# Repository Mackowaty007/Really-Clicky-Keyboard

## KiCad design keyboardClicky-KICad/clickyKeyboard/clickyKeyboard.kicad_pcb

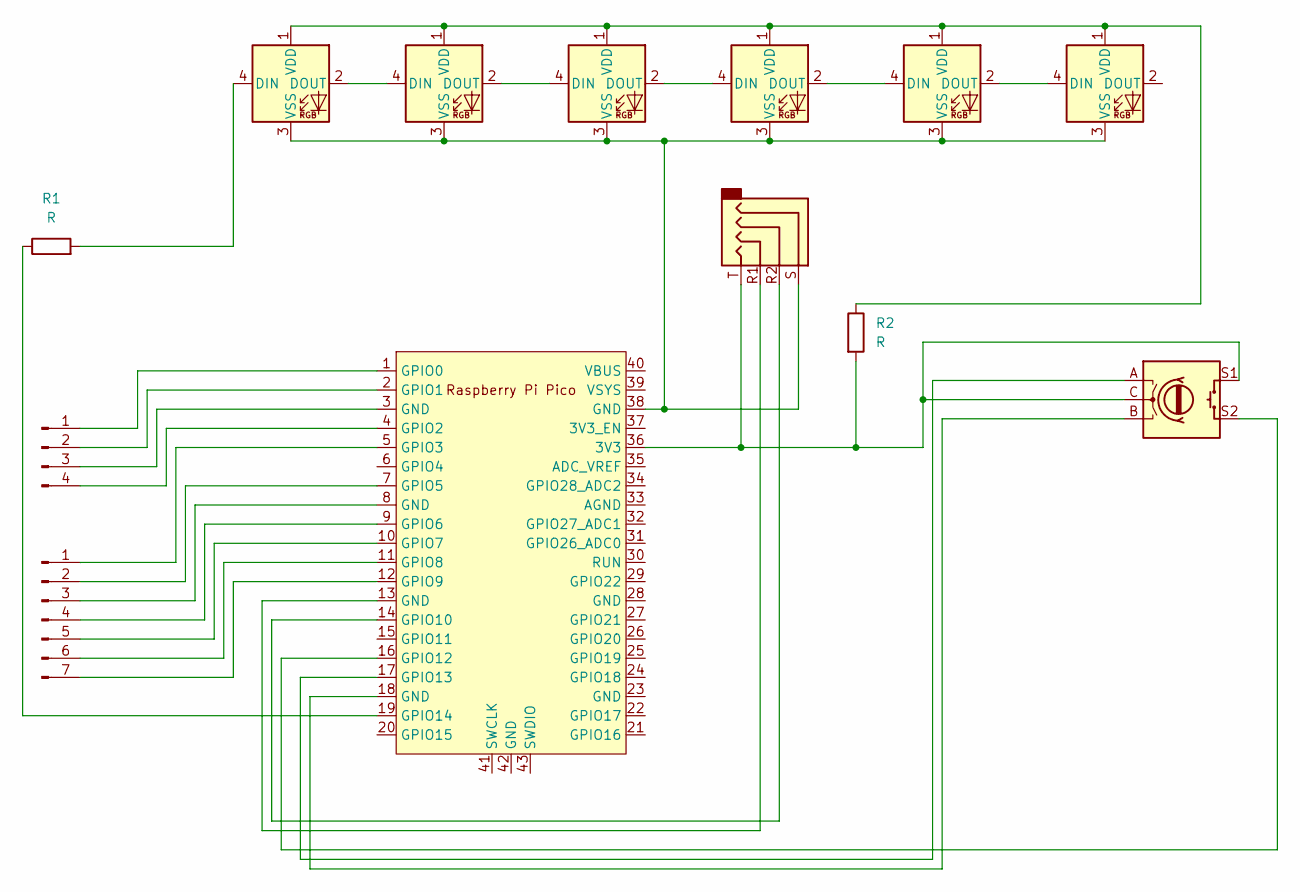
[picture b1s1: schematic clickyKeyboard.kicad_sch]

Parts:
D1, D2, D3, D4, D5, D6: WS2812B; LED_WS2812B_PLCC4_5.0x5.0mm_P3.2mm
J1: Conn_01x04_Pin; PinHeader_1x04_P2.54mm_Vertical
J2: Conn_01x07_Pin; PinHeader_1x07_P2.54mm_Vertical
J4: AudioJack4; Jack_3.5mm_KoreanHropartsElec_PJ-320D-4A_Horizontal
R1, R2: R; R_Axial_DIN0204_L3.6mm_D1.6mm_P7.62mm_Horizontal
SW1: RotaryEncoder_Switch; RotaryEncoder_Alps_EC11E-Switch_Vertical_H20mm
U1: Pico; RPi_Pico_SMD_TH

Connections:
unnamed: D1.4 (DIN), R1.2
unnamed: D1.2 (DOUT), D2.4 (DIN)
unnamed: D1.1 (VDD), D2.1 (VDD), D3.1 (VDD), D4.1 (VDD), D5.1 (VDD), D6.1 (VDD), R2.1
unnamed: D1.3 (VSS), D2.3 (VSS), D3.3 (VSS), D4.3 (VSS), D5.3 (VSS), D6.3 (VSS), J4.S, U1.38 (GND)
unnamed: D2.2 (DOUT), D3.4 (DIN)
unnamed: D3.2 (DOUT), D4.4 (DIN)
unnamed: D4.2 (DOUT), D5.4 (DIN)
unnamed: D5.2 (DOUT), D6.4 (DIN)
unnamed: J1.1, U1.1 (GPIO0)
unnamed: J1.2, U1.2 (GPIO1)
unnamed: J1.3, U1.3 (GND)
unnamed: J1.4, U1.4 (GPIO2)
unnamed: J2.1, U1.5 (GPIO3)
unnamed: J2.2, U1.7 (GPIO5)
unnamed: J2.3, U1.8 (GND)
unnamed: J2.4, U1.9 (GPIO6)
unnamed: J2.5, U1.10 (GPIO7)
unnamed: J2.6, U1.11 (GPIO8)
unnamed: J2.7, U1.12 (GPIO9)
unnamed: J4.R1, U1.13 (GND)
unnamed: SW1.B, U1.18 (GND)
unnamed: J4.T, R2.2, SW1.C, SW1.S1, U1.36 (3V3)
unnamed: J4.R2, U1.14 (GPIO10)
unnamed: SW1.S2, U1.16 (GPIO12)
unnamed: SW1.A, U1.17 (GPIO13)
unnamed: R1.1, U1.19 (GPIO14)

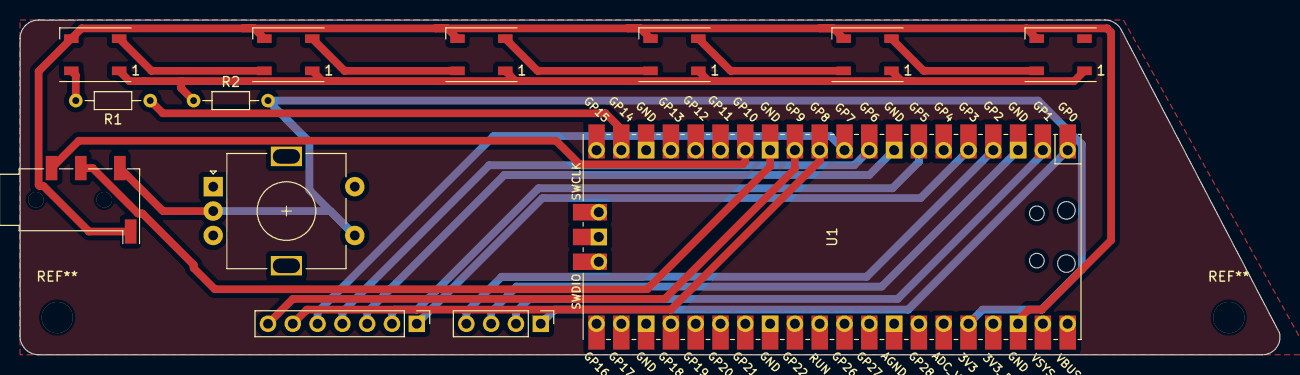
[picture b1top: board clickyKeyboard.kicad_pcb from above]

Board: 2 copper layers, 129.1 x 34.3 mm, 13 parts (0 on the bottom side), 26 nets.
